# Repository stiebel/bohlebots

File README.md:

# Bohlebots
<h2>collection of all published and open source software and hardware from the Bohlebots.</h2>
We are a team of students at the Gymnasium Haan in Germany. We call ourselves Bohlebots
due to the support of the Bohle company at our home town Haan.

We decided to put all our robotic stuff opensource. This includes arduino files and libraries,
eagle pcb files () and eagle libraries (lbr) for all our baords.

See the README files inside the subfolders for further detail.

STILL UNDER CONSTRUCTION

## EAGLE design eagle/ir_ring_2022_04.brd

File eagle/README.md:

<h1>eagle files</h1>
The software "eagle" is a very mature pcb creating software available as a free version (working for a lot off projects) and
educational version available for studenst for free. See the homepage of "eagle pcb".

We decided to use eagle an therefore our pcbs are in this format.

Creating own pcbs for robotics is an issue at the beginning. 
You do make mistakes even if you try hard and creating fully populated boards is rather expensive. Especially if you have to do this several times.
So we decided to create an modular system providing breakout boards for the frequently used features allowing to habe main boards without SMD components.
These pcbs can be purchased at companies worldwide, we get them from JLCPCB.
<br><br>
You will find four files of each project:<br>
XXX.sch : this is the schematics of the board<br>
XXX.brd : this is the layout of the board<br>
XXX.lbr : this is the library you can chose to use this board as a device on your mainboard<br>
XXX.jpg : a picture how it looks like.<br>
<br>
So these are the files provided:

<h2>can-breakout</h2>
We decided to use the can-bus as our major bus system to talk between different boards.
So we need a can-bus controller and soccets for the cable we use.
<br>This is a breakout board to plug in with standard 1/10 inch pins.
<image src=./images/can.jpg>

<h2>taster-LED</h2>
Most robotic projects need buttons and LEDs.
To provide maximum felxibilaty we designed a breakout board with 2 buttons and 2 RGB LEDs and an i2c port expander.
The i2c-address is choosen by short-circuiting pads on the bottom-side of the pcb.
<br>This is a breakout board to plug in with standard 1/10 inch pins.
<image src=./images/can.jpg>
  
<h2>kick</h2>
Most robotic projects need drivers for loads.
We distinguish between two issues: on/off and forward/reverse
This is the on/off board using a High Power FET with including CMOS driver to be controlled by 3.3V
We use this board amongst other things for a kicker of soccer playing robot, so we called this circuit board "kick"
<br>This is a breakout board to plug in with standard 1/10 inch pins.
<image src=./images/can.jpg>
  
<h2>driver</h2>
Most robotic projects need drivers for loads.
We distinguish between two issues: on/off and forward/reverse
This is forward/reverse board using a IFX9201 motor controller to be controlled by 3.3V
We use this board as a standard board to drive dc brushed motors up to 16V/5A.
It includes a overload-protection which switches of the controller before a damage accures.
The controller uses !enabled, direction and pwm to provide full functionallity to proportional
speed settings as well as stop/break and stop/float.
<br>This is a breakout board to plug in with standard 1/10 inch pins.
<image src=./images/can.jpg>

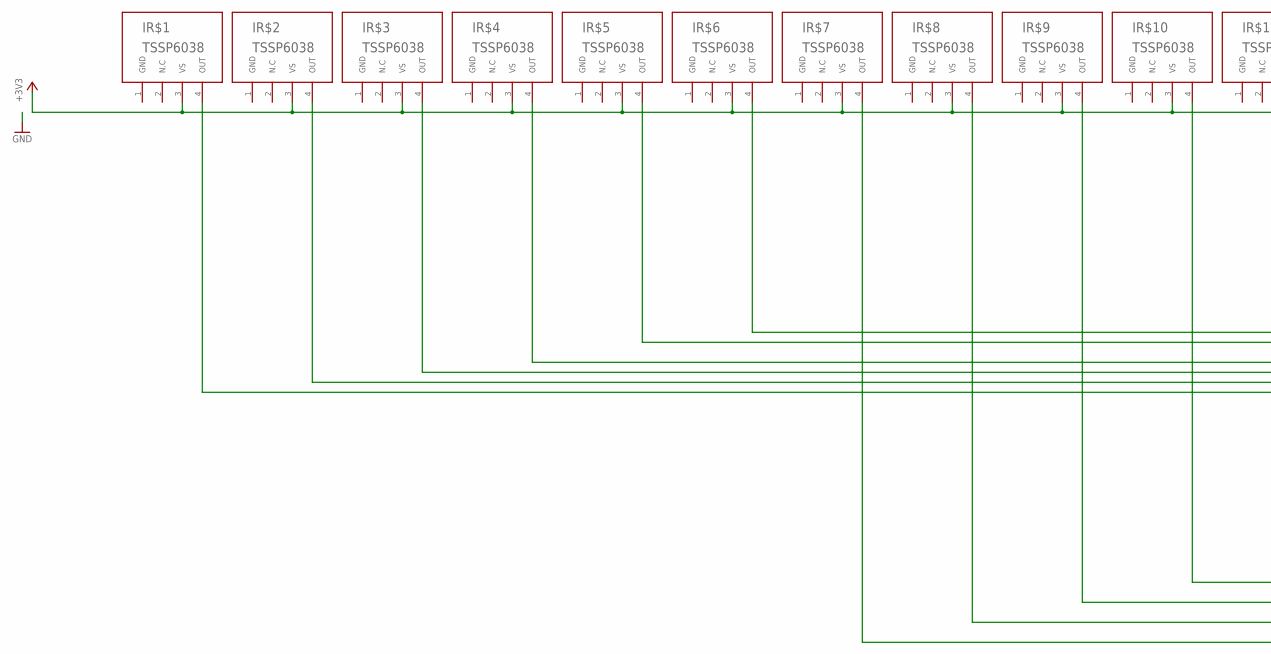
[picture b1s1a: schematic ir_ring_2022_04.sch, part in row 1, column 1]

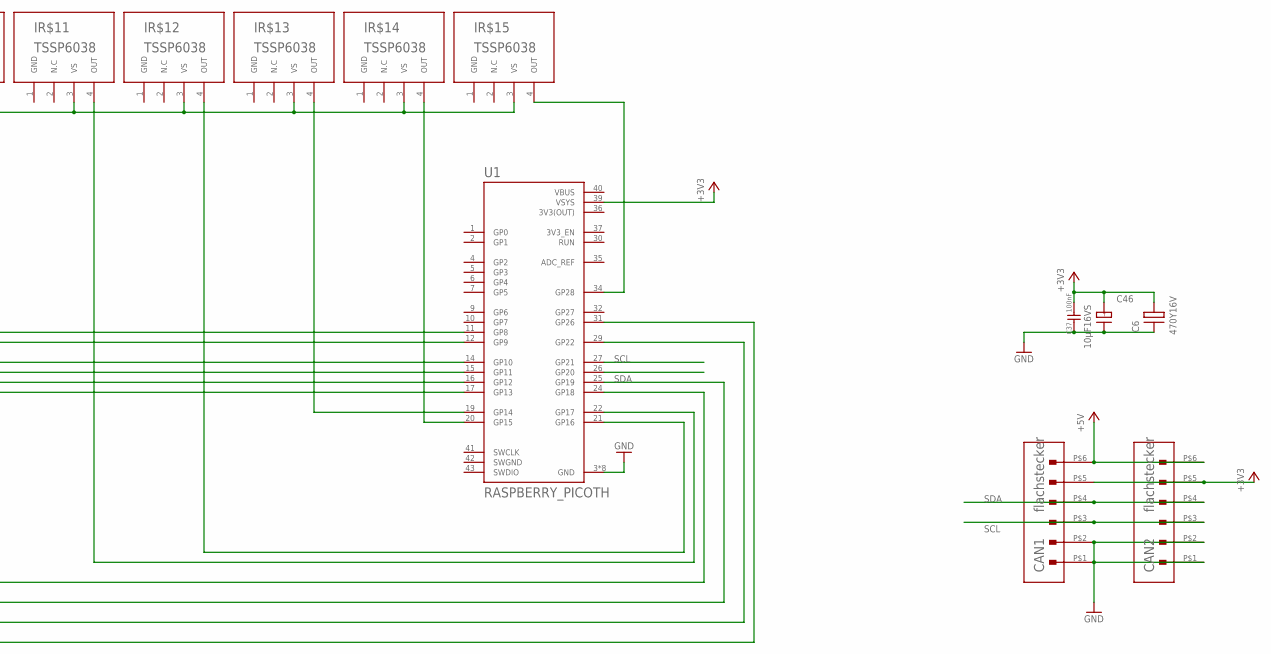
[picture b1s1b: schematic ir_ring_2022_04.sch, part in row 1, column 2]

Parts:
C6: 470Y16V; 150CLZ-1010
C37: 100nF; 0805
C46: 10µF16VS; TANTALC
CAN1, CAN2: flachstecker; MOLEX104078-0610
IR$1, IR$2, IR$3, IR$4, IR$5, IR$6, IR$7, IR$8, IR$9, IR$10, IR$11, IR$12, IR$13, IR$14, IR$15: TSSP6038
U1: RASPBERRY_PICOTH; PICO-PKG-TH

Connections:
3V3(OUT): U1.36 (3V3(OUT))
+3V3: C6.+, C37.1, C46.+, CAN1.P$5 (5), CAN2.P$5 (5), IR$1.3 (VS), IR$2.3 (VS), IR$3.3 (VS), IR$4.3 (VS), IR$5.3 (VS), IR$6.3 (VS), IR$7.3 (VS), IR$8.3 (VS), IR$9.3 (VS), IR$10.3 (VS), IR$11.3 (VS), IR$12.3 (VS), IR$13.3 (VS), IR$14.3 (VS), IR$15.3 (VS), U1.39 (VSYS)
+5V: CAN1.P$6 (6), CAN2.P$6 (6)
GND: C6.-, C37.2, C46.-, CAN1.P$1 (1), CAN1.P$2 (2), CAN2.P$1 (1), CAN2.P$2 (2), IR$1.1 (GND), IR$2.1 (GND), IR$3.1 (GND), IR$4.1 (GND), IR$5.1 (GND), IR$6.1 (GND), IR$7.1 (GND), IR$8.1 (GND), IR$9.1 (GND), IR$10.1 (GND), IR$11.1 (GND), IR$12.1 (GND), IR$13.1 (GND), IR$14.1 (GND), IR$15.1 (GND), U1.3 (GND), U1.8 (GND), U1.13 (GND), U1.18 (GND), U1.23 (GND), U1.28 (GND), U1.33 (GND), U1.38 (GND)
unnamed: IR$1.4 (OUT), U1.17 (GP13)
unnamed: IR$2.4 (OUT), U1.16 (GP12)
unnamed: IR$3.4 (OUT), U1.15 (GP11)
unnamed: IR$4.4 (OUT), U1.14 (GP10)
unnamed: IR$5.4 (OUT), U1.12 (GP9)
unnamed: IR$6.4 (OUT), U1.11 (GP8)
unnamed: IR$7.4 (OUT), U1.31 (GP26)
unnamed: IR$8.4 (OUT), U1.29 (GP22)
unnamed: IR$9.4 (OUT), U1.25 (GP19)
unnamed: IR$10.4 (OUT), U1.24 (GP18)
unnamed: IR$11.4 (OUT), U1.22 (GP17)
unnamed: IR$12.4 (OUT), U1.21 (GP16)
unnamed: IR$14.4 (OUT), U1.20 (GP15)
unnamed: IR$13.4 (OUT), U1.19 (GP14)
unnamed: IR$15.4 (OUT), U1.34 (GP28)
SCL: CAN1.P$3 (3), CAN2.P$3 (3), U1.27 (GP21)
SDA: CAN1.P$4 (4), CAN2.P$4 (4), U1.26 (GP20)
SWGND: U1.42 (SWGND)
VBUS: U1.40 (VBUS)

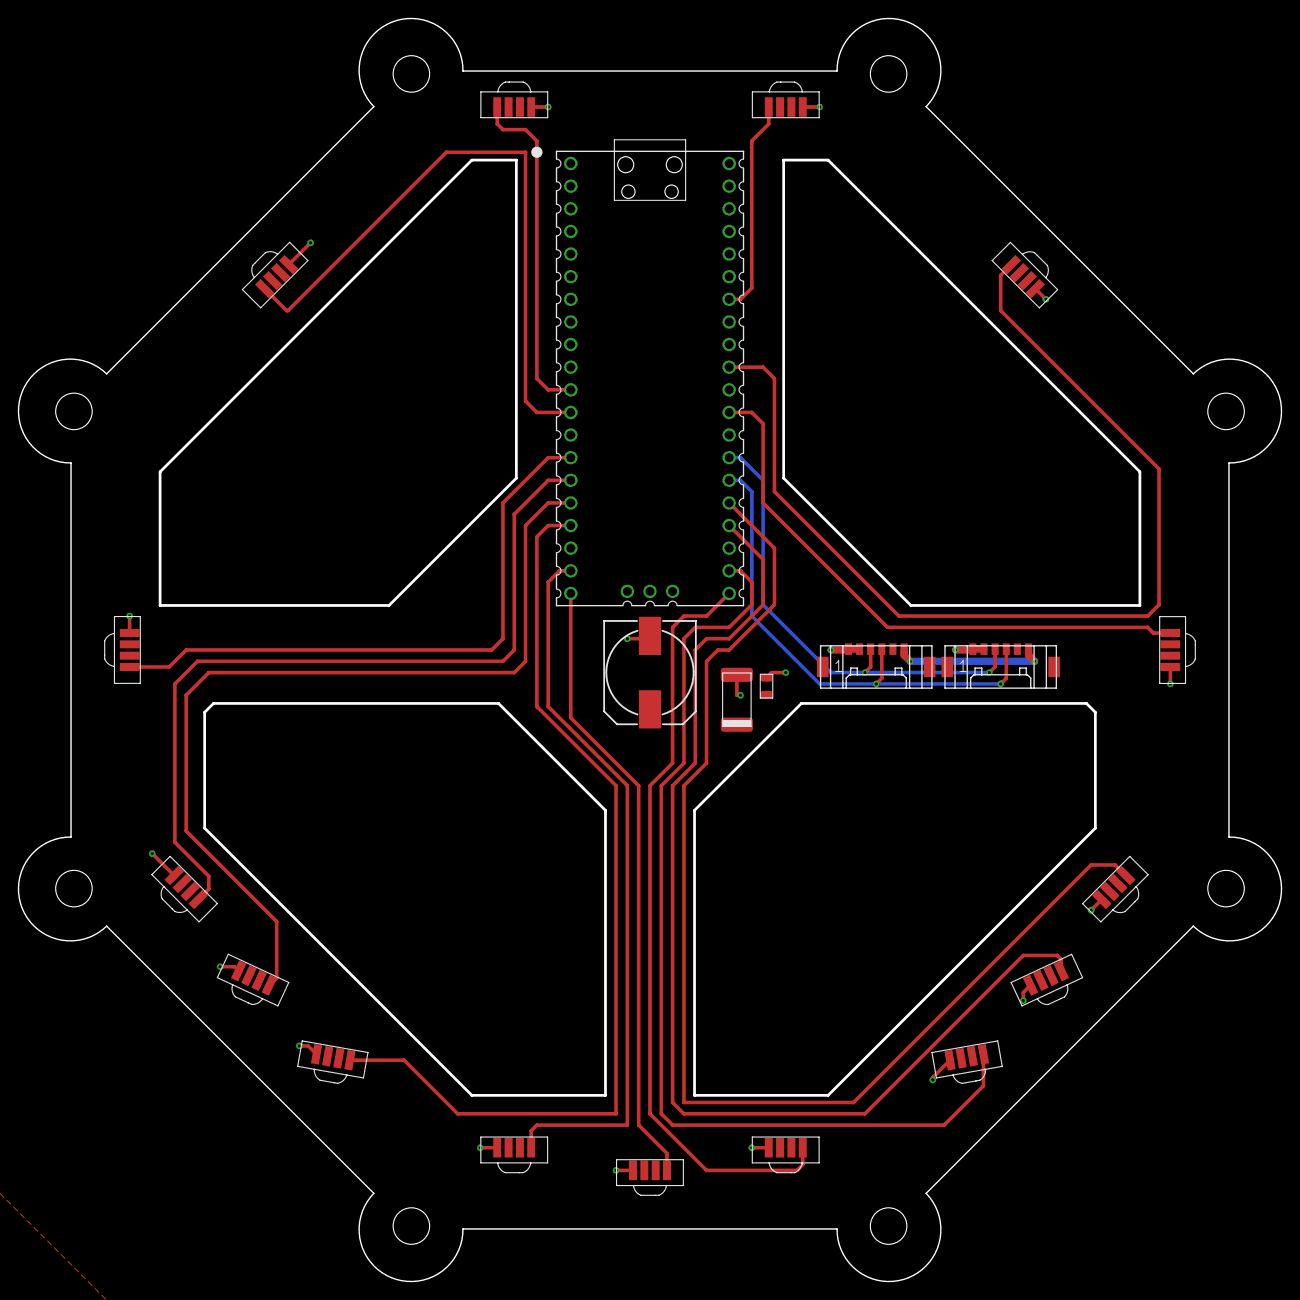
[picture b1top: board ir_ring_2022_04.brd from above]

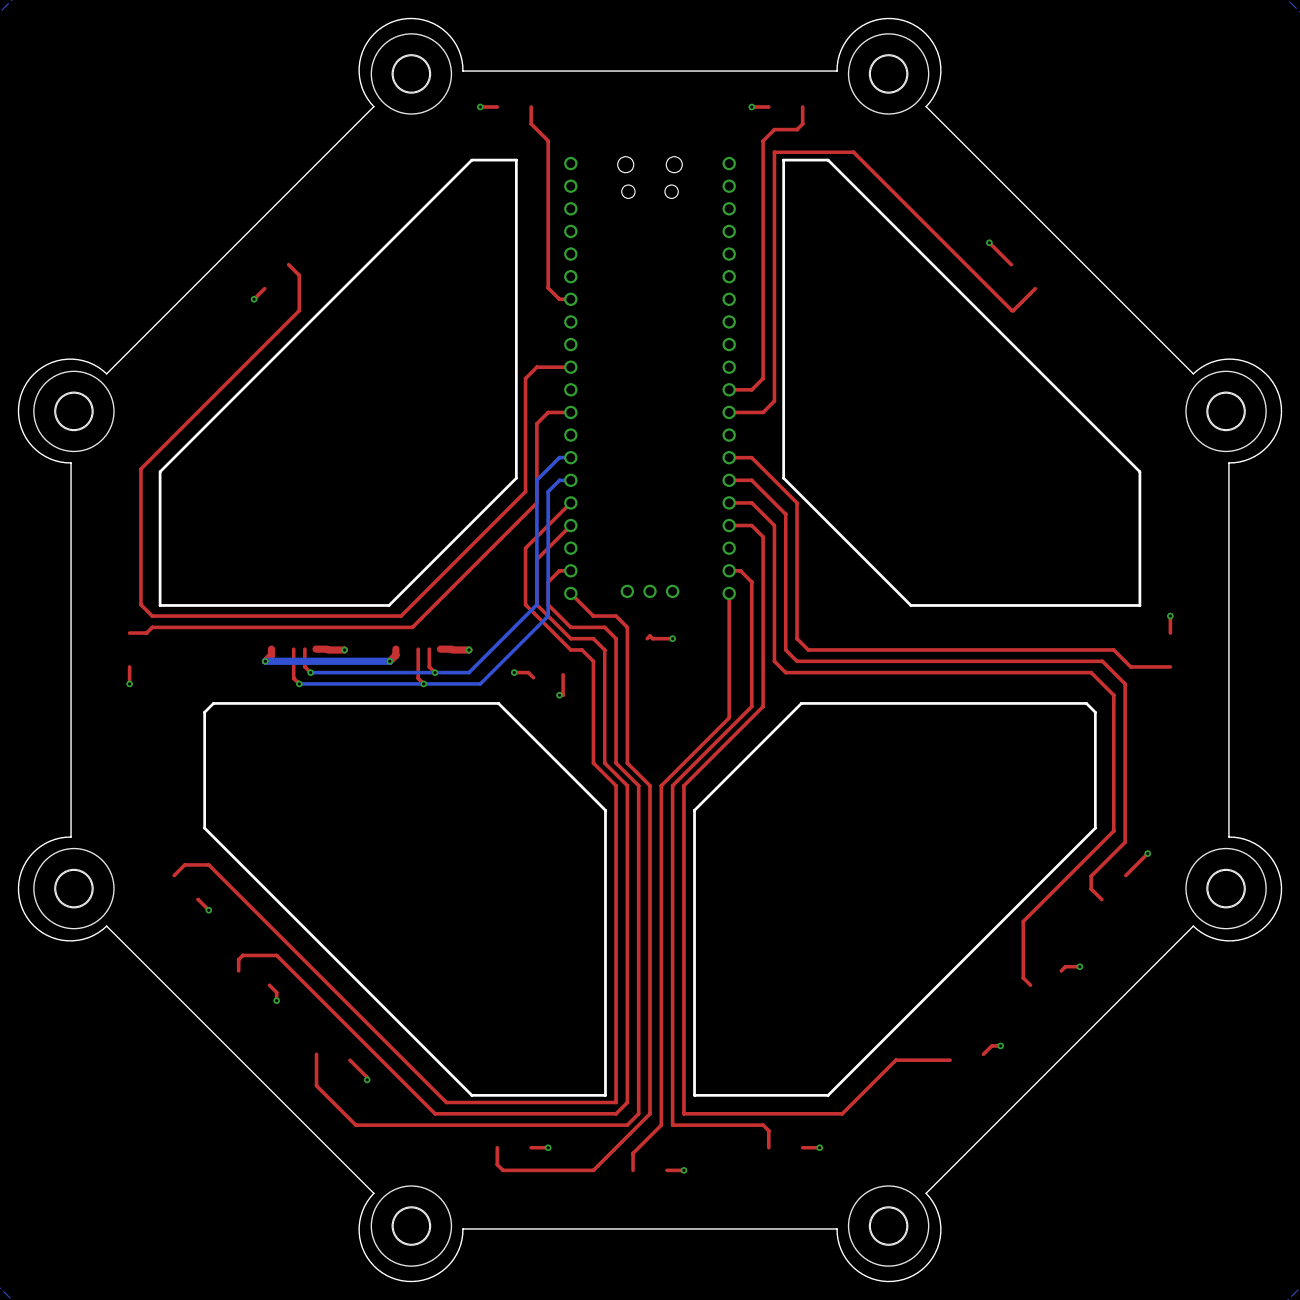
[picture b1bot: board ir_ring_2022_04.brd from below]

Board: 2 copper layers, 141.8 x 141.8 mm, 29 parts (8 on the bottom side), 20 nets.

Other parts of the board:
H1, H2, H3, H4, H5, H6, H7, H8: MOUNT-HOLE4.1; 4,1

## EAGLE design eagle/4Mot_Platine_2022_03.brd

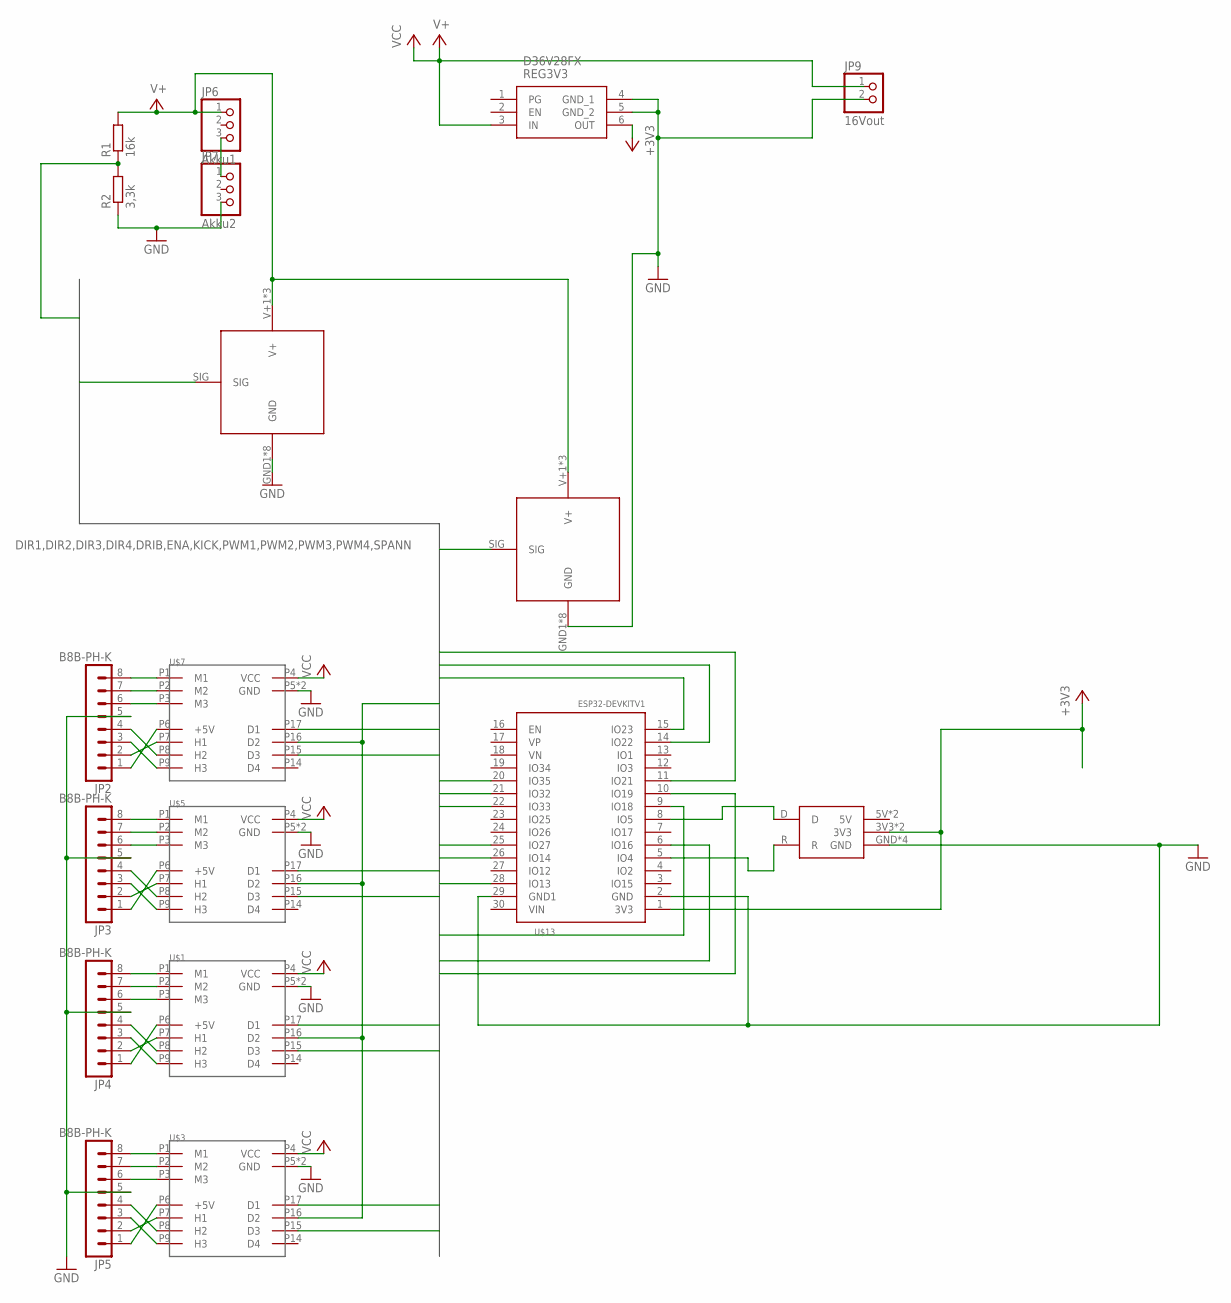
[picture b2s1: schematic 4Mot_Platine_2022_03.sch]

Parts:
JP2, JP3, JP4, JP5: B8B-PH-K
JP6: Akku1; 1X03
JP7: Akku2; 1X03
JP9: 16Vout; 1X02
R1: 16k; 0204/7
R2: 3,3k; 0204/7
REG3V3: D36V28FX
U$1, U$3, U$5, U$7: 24/2
U$13: ESP32DEVKITV1; ESP32-DEVKITV1
U$14, U$15: KICKER
U$18: CANBUS

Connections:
+3V3: REG3V3.6 (OUT), U$13.1 (3V3), U$18.3V3, U$18.3V3_1 (3V3)
D: U$13.8 (IO5), U$18.D
DIR1: U$7.P15 (D3), U$13.25 (IO27)
DIR2: U$5.P15 (D3), U$13.21 (IO32)
DIR3: U$1.P15 (D3), U$13.11 (IO21)
DIR4: U$3.P15 (D3), U$13.9 (IO18)
DRIB: U$13.28 (IO13), U$14.SIG
ENA: U$1.P16 (D2), U$3.P16 (D2), U$5.P16 (D2), U$7.P16 (D2), U$13.15 (IO23)
GND: JP2.5, JP3.5, JP4.5, JP5.5, JP7.3, JP9.2, R2.1, REG3V3.4 (GND_1), REG3V3.5 (GND_2), U$1.P5 (GND), U$1.P18 (GND), U$3.P5 (GND), U$3.P18 (GND), U$5.P5 (GND), U$5.P18 (GND), U$7.P5 (GND), U$7.P18 (GND), U$13.2 (GND), U$13.29 (GND1), U$14.GND1 (GND), U$14.GND2 (GND), U$14.GND3 (GND), U$14.GND4 (GND), U$14.GND5 (GND), U$14.GND6 (GND), U$14.GND7 (GND), U$14.GND8 (GND), U$15.GND1 (GND), U$15.GND2 (GND), U$15.GND3 (GND), U$15.GND4 (GND), U$15.GND5 (GND), U$15.GND6 (GND), U$15.GND7 (GND), U$15.GND8 (GND), U$18.GND, U$18.GND_1 (GND), U$18.GND_2 (GND), U$18.GND_3 (GND)
KICK: U$13.6 (IO16), U$15.SIG
unnamed: JP6.3, JP7.1
unnamed: JP2.8, U$7.P1 (M1)
unnamed: JP2.7, U$7.P2 (M2)
unnamed: JP2.6, U$7.P3 (M3)
unnamed: JP3.8, U$5.P1 (M1)
unnamed: JP3.7, U$5.P2 (M2)
unnamed: JP3.6, U$5.P3 (M3)
unnamed: JP4.8, U$1.P1 (M1)
unnamed: JP4.7, U$1.P2 (M2)
unnamed: JP4.6, U$1.P3 (M3)
unnamed: JP5.8, U$3.P1 (M1)
unnamed: JP5.7, U$3.P2 (M2)
unnamed: JP5.6, U$3.P3 (M3)
unnamed: JP2.2, U$7.P7 (H1)
unnamed: JP2.3, U$7.P9 (H3)
unnamed: JP2.4, U$7.P8 (H2)
unnamed: JP3.2, U$5.P7 (H1)
unnamed: JP3.3, U$5.P9 (H3)
unnamed: JP3.4, U$5.P8 (H2)
unnamed: JP4.2, U$1.P7 (H1)
unnamed: JP4.3, U$1.P9 (H3)
unnamed: JP4.4, U$1.P8 (H2)
unnamed: JP5.2, U$3.P7 (H1)
unnamed: JP5.3, U$3.P9 (H3)
unnamed: JP5.4, U$3.P8 (H2)
unnamed: JP2.1, U$7.P6 (+5V)
unnamed: JP3.1, U$5.P6 (+5V)
unnamed: JP4.1, U$1.P6 (+5V)
unnamed: JP5.1, U$3.P6 (+5V)
PWM1: U$7.P17 (D1), U$13.26 (IO14)
PWM2: U$5.P17 (D1), U$13.22 (IO33)
PWM3: U$1.P17 (D1), U$13.14 (IO22)
PWM4: U$3.P17 (D1), U$13.10 (IO19)
R: U$13.5 (IO4), U$18.R
SPANN: R1.1, R2.2, U$13.20 (IO35)
V+: JP6.1, JP9.1, R1.2, REG3V3.3 (IN), U$1.P4 (VCC), U$3.P4 (VCC), U$5.P4 (VCC), U$7.P4 (VCC), U$14.V+1 (V+), U$14.V+2 (V+), U$14.V+3 (V+), U$15.V+1 (V+), U$15.V+2 (V+), U$15.V+3 (V+)

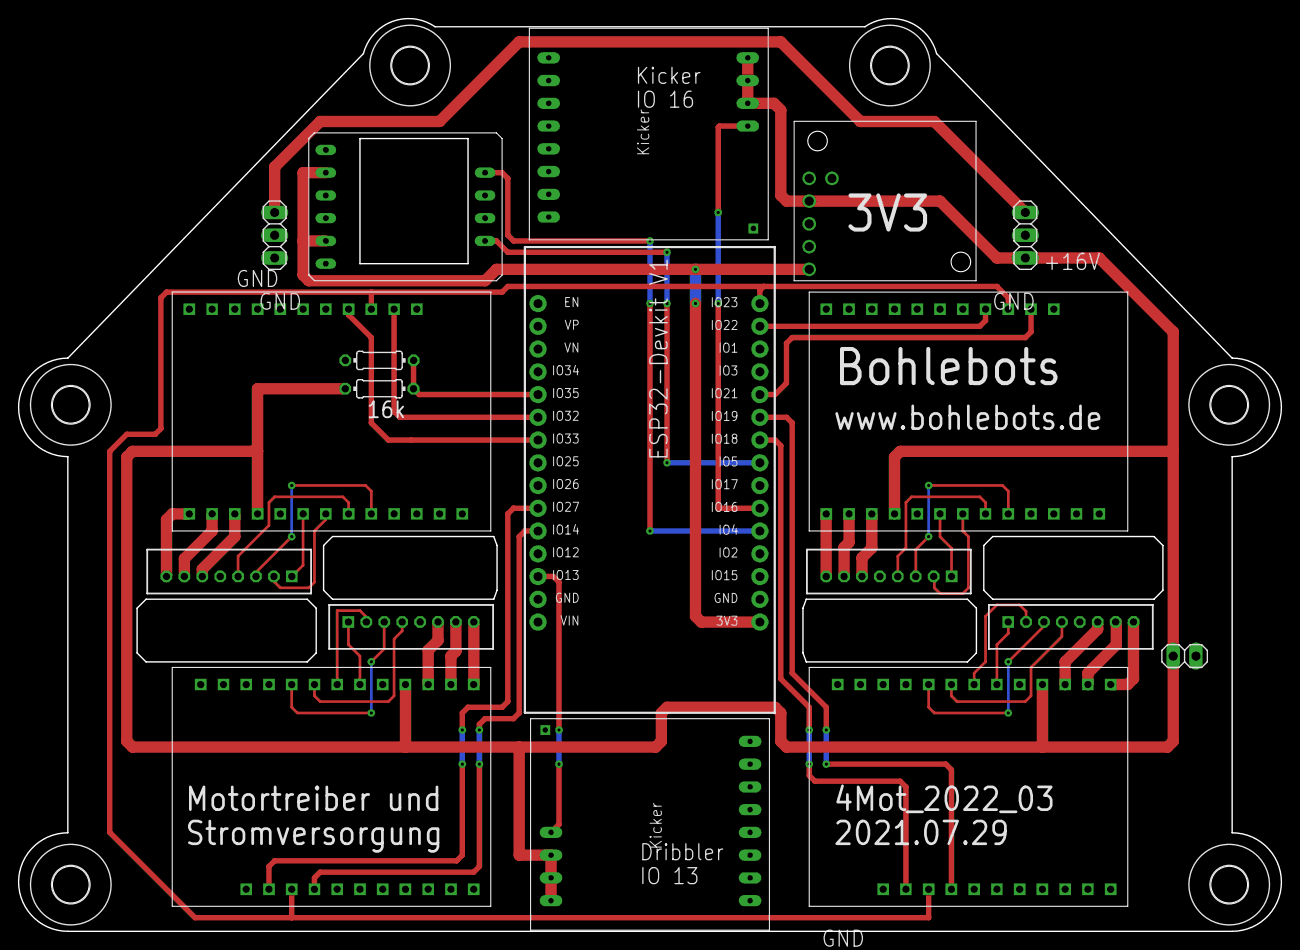
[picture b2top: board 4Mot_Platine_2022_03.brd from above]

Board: 2 copper layers, 141.0 x 101.9 mm, 24 parts (0 on the bottom side), 46 nets.

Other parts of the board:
U$2, U$4, U$6, U$9, U$10, U$12: 4,1

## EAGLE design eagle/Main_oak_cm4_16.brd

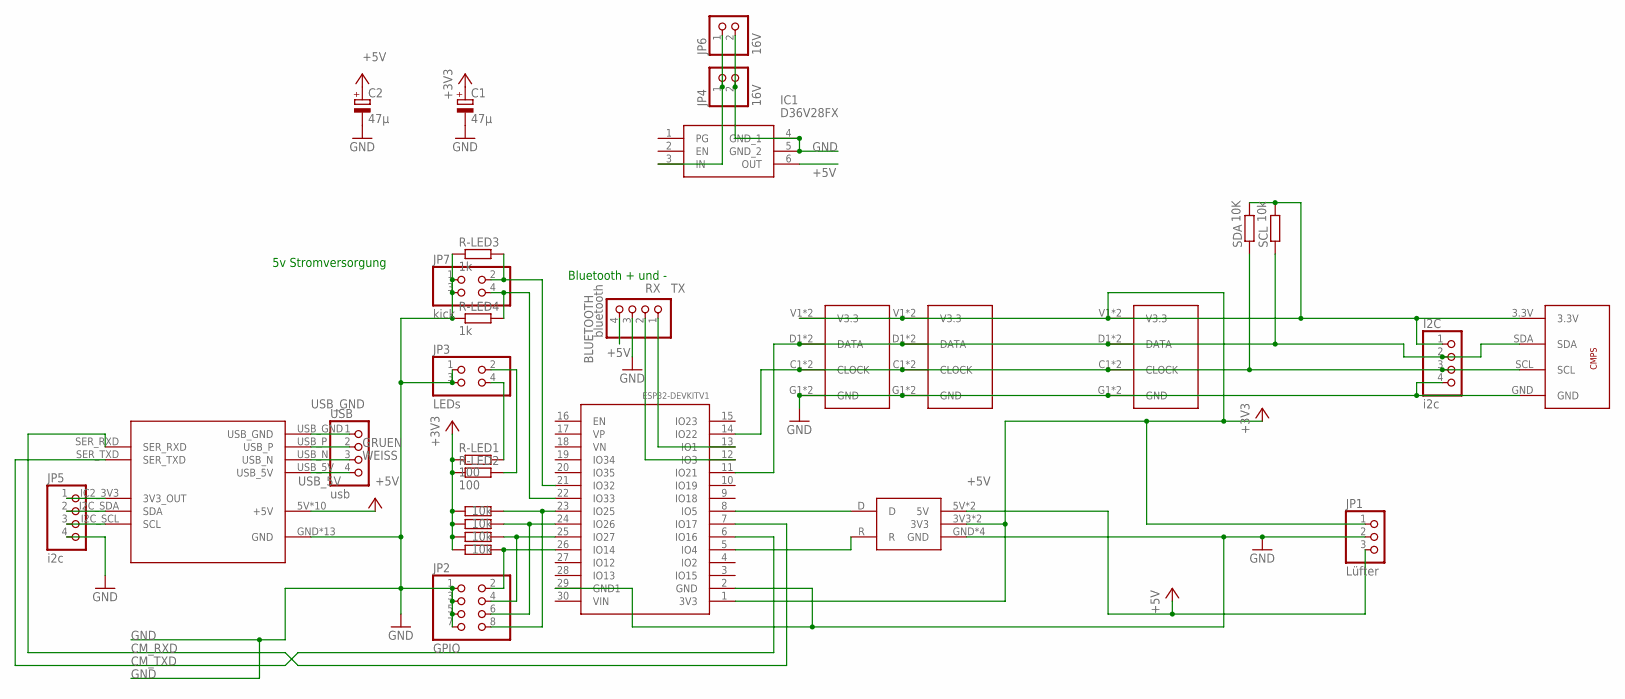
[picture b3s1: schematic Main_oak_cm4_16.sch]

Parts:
BLUETOOTH: bluetooth; 1X04
C1, C2: 47µ; E2,5-6E
I2C: i2c; 1X04
IC1: D36V28FX
JP1: Lüfter; 1X03
JP2: GPIO; 2X04
JP3: LEDs; 2X02
JP4, JP6: 16V; 1X02
JP5: i2c; 1X04
JP7: kick; 2X02
R-LED1, R-LED2: 100; 0207/10
R-LED3, R-LED4: 1k; 0207/10
R_AD14, R_AD25, R_AD26, R_AD27: 10k; 0207/10
SCL: 10k; 0207/10
SDA: 10K; 0207/10
U$1, U$3, U$7: TASTER_LED
U$5: CM4-ADAPTER
U$8: CMPS
U$11: CANBUS
U$13: ESP32DEVKITV1; ESP32-DEVKITV1
USB: usb; 1X04

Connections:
+3V3: C1.+, I2C.1, JP1.1, R-LED1.1, R-LED2.1, R_AD14.1, R_AD25.1, R_AD26.1, R_AD27.1, SCL.2, SDA.2, U$1.V1 (V3.3), U$1.V2 (V3.3), U$3.V1 (V3.3), U$3.V2 (V3.3), U$7.V1 (V3.3), U$7.V2 (V3.3), U$8.3.3V, U$11.3V3, U$11.3V3_1 (3V3), U$13.1 (3V3)
+5V: BLUETOOTH.4, C2.+, IC1.6 (OUT), JP1.3, U$5.5V (+5V), U$5.5V.1 (+5V), U$5.5V.2 (+5V), U$5.5V.3 (+5V), U$5.5V.4 (+5V), U$5.5V.5 (+5V), U$5.5V.6 (+5V), U$5.5V.7 (+5V), U$5.5V.8 (+5V), U$5.5V.9 (+5V), U$11.5V, U$11.5V_1 (5V)
CLOCK: I2C.3, SDA.1, U$1.C1 (CLOCK), U$1.C2 (CLOCK), U$3.C1 (CLOCK), U$3.C2 (CLOCK), U$7.C1 (CLOCK), U$7.C2 (CLOCK), U$8.SCL, U$13.14 (IO22)
CM_RXD: U$5.SER_RXD, U$13.7 (IO17)
CM_TXD: U$5.SER_TXD, U$13.6 (IO16)
D: U$11.D, U$13.8 (IO5)
DATA: I2C.2, SCL.1, U$1.D1 (DATA), U$1.D2 (DATA), U$3.D1 (DATA), U$3.D2 (DATA), U$7.D1 (DATA), U$7.D2 (DATA), U$8.SDA, U$13.11 (IO21)
GND: BLUETOOTH.3, C1.-, C2.-, I2C.4, IC1.4 (GND_1), IC1.5 (GND_2), JP1.2, JP2.1, JP2.3, JP2.5, JP2.7, JP3.1, JP3.3, JP4.2, JP5.4, JP6.2, JP7.1, JP7.3, R-LED3.1, R-LED4.1, U$1.G1 (GND), U$1.G2 (GND), U$3.G1 (GND), U$3.G2 (GND), U$5.GND, U$5.GND1 (GND), U$5.GND2 (GND), U$5.GND3 (GND), U$5.GND4 (GND), U$5.GND5 (GND), U$5.GND6 (GND), U$5.GND7 (GND), U$5.GND8 (GND), U$5.GND9 (GND), U$5.I2C_GND (GND), U$5.SER_GND (GND), U$5.SER_GND2 (GND), U$7.G1 (GND), U$7.G2 (GND), U$8.GND, U$11.GND, U$11.GND_1 (GND), U$11.GND_2 (GND), U$11.GND_3 (GND), U$13.2 (GND), U$13.29 (GND1)
GRUEN: U$5.USB_P, USB.2
IO14: JP2.2, R_AD14.2, U$13.26 (IO14)
IO25: JP2.8, R_AD25.2, U$13.23 (IO25)
IO26: JP2.6, R_AD26.2, U$13.24 (IO26)
IO27: JP2.4, R_AD27.2, U$13.25 (IO27)
IO32: JP7.2, R-LED3.2, U$13.21 (IO32)
IO33: JP7.4, R-LED4.2, U$13.22 (IO33)
unnamed: IC1.3 (IN), JP4.1, JP6.1
unnamed: JP3.4, R-LED1.2
unnamed: JP3.2, R-LED2.2
unnamed: JP5.1, U$5.IC2_3V3 (3V3_OUT)
unnamed: JP5.2, U$5.I2C_SDA (SDA)
unnamed: JP5.3, U$5.I2C_SCL (SCL)
R: U$11.R, U$13.5 (IO4)
RX: BLUETOOTH.2, U$13.12 (IO3)
TX: BLUETOOTH.1, U$13.13 (IO1)
USB_5V: U$5.USB_5V, USB.4
USB_GND: U$5.USB_GND, USB.1
WEISS: U$5.USB_N, USB.3

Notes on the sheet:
Bluetooth + und -
5v Stromversorgung

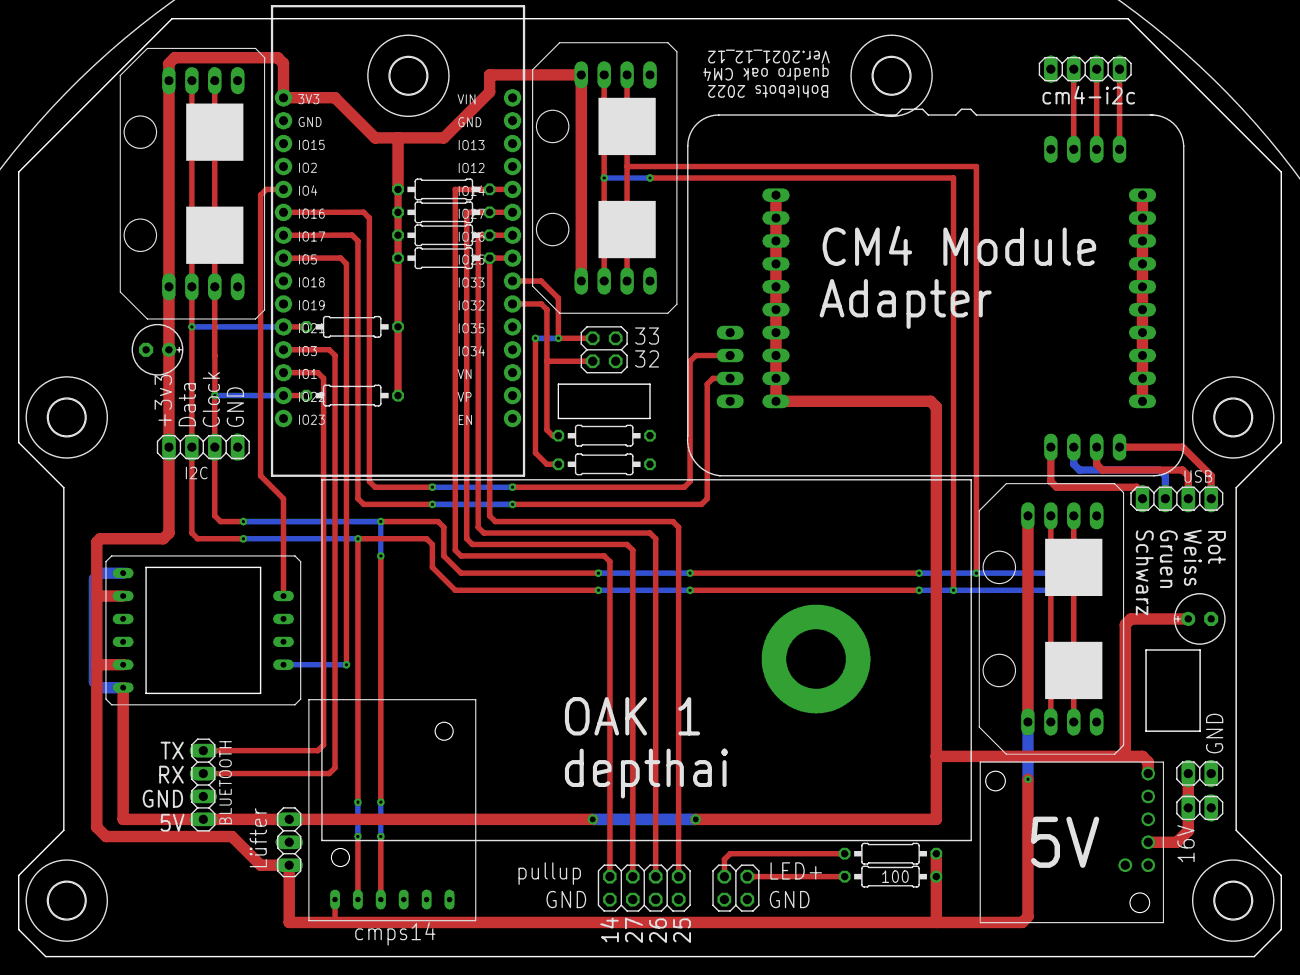
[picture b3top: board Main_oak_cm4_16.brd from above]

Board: 2 copper layers, 140.0 x 104.0 mm, 36 parts (0 on the bottom side), 27 nets.

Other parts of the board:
U$2, U$4, U$6, U$9, U$10, U$12: 4,1

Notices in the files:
parts and their libraries:
con-jst-ph: Copyright (C) 2016, Bob Starr
esp32: Creative Commons Attribution-ShareAlike 4.0 International
